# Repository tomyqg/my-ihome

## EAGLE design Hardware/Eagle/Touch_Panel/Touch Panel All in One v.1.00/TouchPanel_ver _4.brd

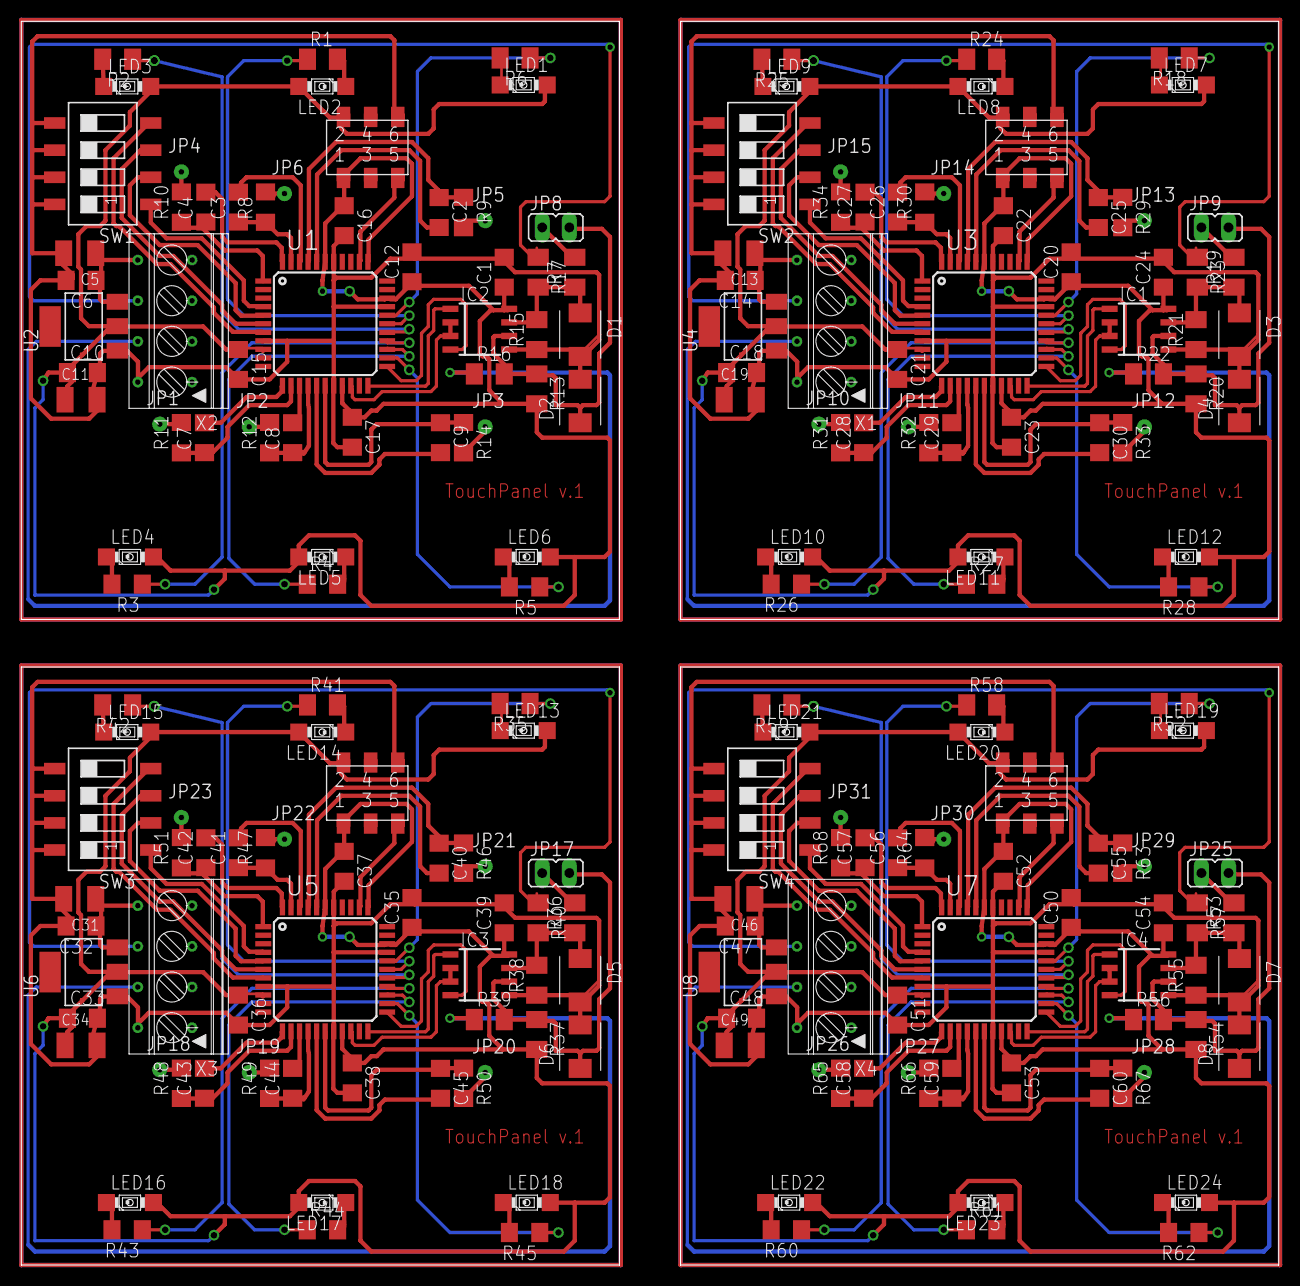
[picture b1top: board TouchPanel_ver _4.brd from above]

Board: 2 copper layers, 117.7 x 116.5 mm, 212 parts (0 on the bottom side), 188 nets.

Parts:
C1, C6, C10, C12, C14, C15, C16, C17, C18, C20, C21, C22, C23, C24, C32, C33, C35, C36, C37, C38, C39, C47, C48, C50, C51, C52, C53, C54: 100n; C1206
C2, C3, C4, C7, C8, C9, C25, C26, C27, C28, C29, C30, C40, C41, C42, C43, C44, C45, C55, C56, C57, C58, C59, C60: 22n; C1206
C5, C11, C13, C19, C31, C34, C46, C49: 10u/16; SMC_B
D1, D2, D3, D4, D5, D6, D7, D8: SMBJ
IC1, IC2, IC3, IC4: ST3485; D_R-PDSO-G8
JP1, JP2, JP3, JP4, JP5, JP6, JP10, JP11, JP12, JP13, JP14, JP15, JP18, JP19, JP20, JP21, JP22, JP23, JP26, JP27, JP28, JP29, JP30, JP31: 1X01
JP7, JP16, JP24, JP32: PINHD-2X3_SMDSMD; 2X03_SMD
JP8, JP9, JP17, JP25: terminator; JP1
LED1, LED2, LED3, LED4, LED5, LED6, LED7, LED8, LED9, LED10, LED11, LED12, LED13, LED14, LED15, LED16, LED17, LED18, LED19, LED20, LED21, LED22, LED23, LED24: green; MINI-TOPLED-SANTANA
R1, R2, R6, R18, R24, R25, R35, R41, R42, R52, R58, R59: 220; M1206
R3, R4, R5, R26, R27, R28, R43, R44, R45, R60, R61, R62: 220; R1206
R7, R19, R36, R53: 130R; M1206
R8, R9, R10, R11, R12, R14, R29, R30, R31, R32, R33, R34, R46, R47, R48, R49, R50, R51, R63, R64, R65, R66, R67, R68: 10k; R1206
R13, R15, R20, R21, R37, R38, R54, R55: 750R; M1206
R16, R17, R22, R23, R39, R40, R56, R57: 10R; M1206
SW1, SW2, SW3, SW4: SWS004; SMS-004
U1, U3, U5, U7: XMEGA-A4TQFP; TQFP44
U2, U4, U6, U8: SPX1117M3-L-3-3; SOT223
X1, X2, X3, X4: 1705566

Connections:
+3V1: C18.1, C19.+, C20.1, C21.1, C22.1, C23.1, C24.1, IC1.8, JP16.2, LED7.A, LED8.A, LED9.A, LED10.A, LED11.A, LED12.A, R20.2, U3.9, U3.19, U3.31, U3.39, U4.2
+3V2: C33.1, C34.+, C35.1, C36.1, C37.1, C38.1, C39.1, IC3.8, JP24.2, LED13.A, LED14.A, LED15.A, LED16.A, LED17.A, LED18.A, R37.2, U5.9, U5.19, U5.31, U5.39, U6.2
+3V3: C1.1, C10.1, C11.+, C12.1, C15.1, C16.1, C17.1, IC2.8, JP7.2, LED1.A, LED2.A, LED3.A, LED4.A, LED5.A, LED6.A, R13.2, U1.9, U1.19, U1.31, U1.39, U2.2
+3V4: C48.1, C49.+, C50.1, C51.1, C52.1, C53.1, C54.1, IC4.8, JP32.2, LED19.A, LED20.A, LED21.A, LED22.A, LED23.A, LED24.A, R54.2, U7.9, U7.19, U7.31, U7.39, U8.2
+5V: C5.+, C6.1, U2.3, X2.4.2
+5V1: C13.+, C14.1, U4.3, X1.4.2
+5V2: C31.+, C32.1, U6.3, X3.4.2
+5V3: C46.+, C47.1, U8.3, X4.4.2
GND: C1.2, C5.-, C6.2, C10.2, C11.-, C12.2, C15.2, C16.2, C17.2, D1.A, D2.A, IC2.5, JP7.6, R15.1, SW1.5, SW1.6, SW1.7, SW1.8, U1.8, U1.18, U1.30, U1.38, U2.1, X2.1.2
GND1: C13.-, C14.2, C18.2, C19.-, C20.2, C21.2, C22.2, C23.2, C24.2, D3.A, D4.A, IC1.5, JP16.6, R21.1, SW2.5, SW2.6, SW2.7, SW2.8, U3.8, U3.18, U3.30, U3.38, U4.1, X1.1.2
GND2: C31.-, C32.2, C33.2, C34.-, C35.2, C36.2, C37.2, C38.2, C39.2, D5.A, D6.A, IC3.5, JP24.6, R38.1, SW3.5, SW3.6, SW3.7, SW3.8, U5.8, U5.18, U5.30, U5.38, U6.1, X3.1.2
GND3: C46.-, C47.2, C48.2, C49.-, C50.2, C51.2, C52.2, C53.2, C54.2, D7.A, D8.A, IC4.5, JP32.6, R55.1, SW4.5, SW4.6, SW4.7, SW4.8, U7.8, U7.18, U7.30, U7.38, U8.1, X4.1.2
JP1: JP1.1, R11.2
JP2: JP2.1, R12.2
JP3: JP3.1, R14.2
JP4: JP4.1, R10.2
JP5: JP5.1, R9.2
JP6: JP6.1, R8.2
JP7: JP10.1, R31.2
JP8: JP11.1, R32.2
JP9: JP12.1, R33.2
JP10: JP13.1, R29.2
JP11: JP15.1, R34.2
JP12: JP14.1, R30.2
JP13: JP18.1, R48.2
JP14: JP19.1, R49.2
JP15: JP20.1, R50.2
JP16: JP21.1, R46.2
JP17: JP23.1, R51.2
JP18: JP22.1, R47.2
JP19: JP26.1, R65.2
JP20: JP27.1, R66.2
JP21: JP28.1, R67.2
JP22: JP29.1, R63.2
JP23: JP31.1, R68.2
JP24: JP30.1, R64.2
unnamed: LED2.C, R1.2
unnamed: LED3.C, R2.2
unnamed: LED4.C, R3.2
unnamed: LED5.C, R4.2
unnamed: LED6.C, R5.2
unnamed: R17.1, X2.3.2
unnamed: JP8.1, R7.2
unnamed: R16.1, X2.2.2
unnamed: D1.C, IC2.7, R7.1, R15.2, R17.2
unnamed: JP7.1, U1.34
unnamed: JP7.5, U1.35
unnamed: LED1.C, R6.2
unnamed: C2.1, R9.1, U1.41
unnamed: C2.2, U1.40
unnamed: C9.2, U1.16
unnamed: C3.1, R8.1, U1.43
unnamed: C8.2, U1.14
unnamed: C4.1, R10.1, U1.1
unnamed: C7.2, U1.12
unnamed: C9.1, R14.1, U1.17
unnamed: SW1.1, U1.4
unnamed: SW1.4, U1.7
unnamed: SW1.2, U1.5
unnamed: SW1.3, U1.6
unnamed: C8.1, R12.1, U1.15
unnamed: C3.2, U1.42
unnamed: C7.1, R11.1, U1.13
unnamed: C4.2, U1.44
unnamed: LED7.C, R18.2
unnamed: JP9.1, R19.2
unnamed: D3.C, IC1.7, R19.1, R21.2, R23.2
unnamed: LED8.C, R24.2
unnamed: LED9.C, R25.2
unnamed: LED10.C, R26.2
unnamed: LED11.C, R27.2
unnamed: LED12.C, R28.2
unnamed: C25.1, R29.1, U3.41
unnamed: C25.2, U3.40
unnamed: C26.1, R30.1, U3.43
unnamed: C27.1, R34.1, U3.1
unnamed: C30.1, R33.1, U3.17
unnamed: C29.1, R32.1, U3.15
unnamed: C28.1, R31.1, U3.13
unnamed: C30.2, U3.16
unnamed: C29.2, U3.14
unnamed: C28.2, U3.12
unnamed: C26.2, U3.42
unnamed: C27.2, U3.44
unnamed: JP16.1, U3.34
unnamed: JP16.5, U3.35
unnamed: SW2.1, U3.4
unnamed: SW2.4, U3.7
unnamed: SW2.2, U3.5
unnamed: SW2.3, U3.6
unnamed: R23.1, X1.3.2
unnamed: R22.1, X1.2.2
unnamed: LED13.C, R35.2
unnamed: JP17.1, R36.2
unnamed: D5.C, IC3.7, R36.1, R38.2, R40.2
unnamed: LED14.C, R41.2
unnamed: LED15.C, R42.2
unnamed: LED16.C, R43.2
unnamed: LED17.C, R44.2
unnamed: LED18.C, R45.2
unnamed: C40.1, R46.1, U5.41
unnamed: C40.2, U5.40
unnamed: C41.1, R47.1, U5.43
unnamed: C42.1, R51.1, U5.1
unnamed: C45.1, R50.1, U5.17
unnamed: C44.1, R49.1, U5.15
unnamed: C43.1, R48.1, U5.13
unnamed: C45.2, U5.16
unnamed: C44.2, U5.14
unnamed: C43.2, U5.12
unnamed: C41.2, U5.42
unnamed: C42.2, U5.44
unnamed: JP24.1, U5.34
unnamed: JP24.5, U5.35
unnamed: SW3.1, U5.4
unnamed: SW3.4, U5.7
unnamed: SW3.2, U5.5
unnamed: SW3.3, U5.6
unnamed: R40.1, X3.3.2
unnamed: R39.1, X3.2.2
unnamed: LED19.C, R52.2
unnamed: JP25.1, R53.2
unnamed: D7.C, IC4.7, R53.1, R55.2, R57.2
unnamed: LED20.C, R58.2
unnamed: LED21.C, R59.2
unnamed: LED22.C, R60.2
unnamed: LED23.C, R61.2
unnamed: LED24.C, R62.2
unnamed: C55.1, R63.1, U7.41
unnamed: C55.2, U7.40
unnamed: C56.1, R64.1, U7.43
unnamed: C57.1, R68.1, U7.1
unnamed: C60.1, R67.1, U7.17
unnamed: C59.1, R66.1, U7.15
unnamed: C58.1, R65.1, U7.13
unnamed: C60.2, U7.16
unnamed: C59.2, U7.14
unnamed: C58.2, U7.12
unnamed: C56.2, U7.42
unnamed: C57.2, U7.44
unnamed: JP32.1, U7.34
unnamed: JP32.5, U7.35
unnamed: SW4.1, U7.4
unnamed: SW4.4, U7.7
unnamed: SW4.2, U7.5
unnamed: SW4.3, U7.6
unnamed: R57.1, X4.3.2
unnamed: R56.1, X4.2.2
PD_0: IC2.2, IC2.3, U1.20
PD_1: IC1.2, IC1.3, U3.20
PD_2: IC2.1, U1.22
PD_3: IC2.4, U1.23
PD_4: R5.1, U1.24
PD_5: R4.1, U1.25
PD_6: R3.1, U1.26
PD_7: R2.1, U1.27
PD_8: IC1.1, U3.22
PD_9: IC1.4, U3.23
PD_10: R28.1, U3.24
PD_11: R27.1, U3.25
PD_12: R26.1, U3.26
PD_13: R25.1, U3.27
PD_14: IC3.2, IC3.3, U5.20
PD_15: IC3.1, U5.22
PD_16: IC3.4, U5.23
PD_17: R45.1, U5.24
PD_18: R44.1, U5.25
PD_19: R43.1, U5.26
PD_20: R42.1, U5.27
PD_21: IC4.2, IC4.3, U7.20
PD_22: IC4.1, U7.22
PD_23: IC4.4, U7.23
PD_24: R62.1, U7.24
PD_25: R61.1, U7.25
PD_26: R60.1, U7.26
PD_27: R59.1, U7.27
PE_0: R1.1, U1.28
PE_1: R6.1, U1.29
PE_2: R24.1, U3.28
PE_3: R18.1, U3.29
PE_4: R41.1, U5.28
PE_5: R35.1, U5.29
PE_6: R58.1, U7.28
PE_7: R52.1, U7.29
RS485_A1: D2.C, IC2.6, JP8.2, R13.1, R16.2
RS485_A2: D4.C, IC1.6, JP9.2, R20.1, R22.2
RS485_A3: D6.C, IC3.6, JP17.2, R37.1, R39.2
RS485_A4: D8.C, IC4.6, JP25.2, R54.1, R56.2
